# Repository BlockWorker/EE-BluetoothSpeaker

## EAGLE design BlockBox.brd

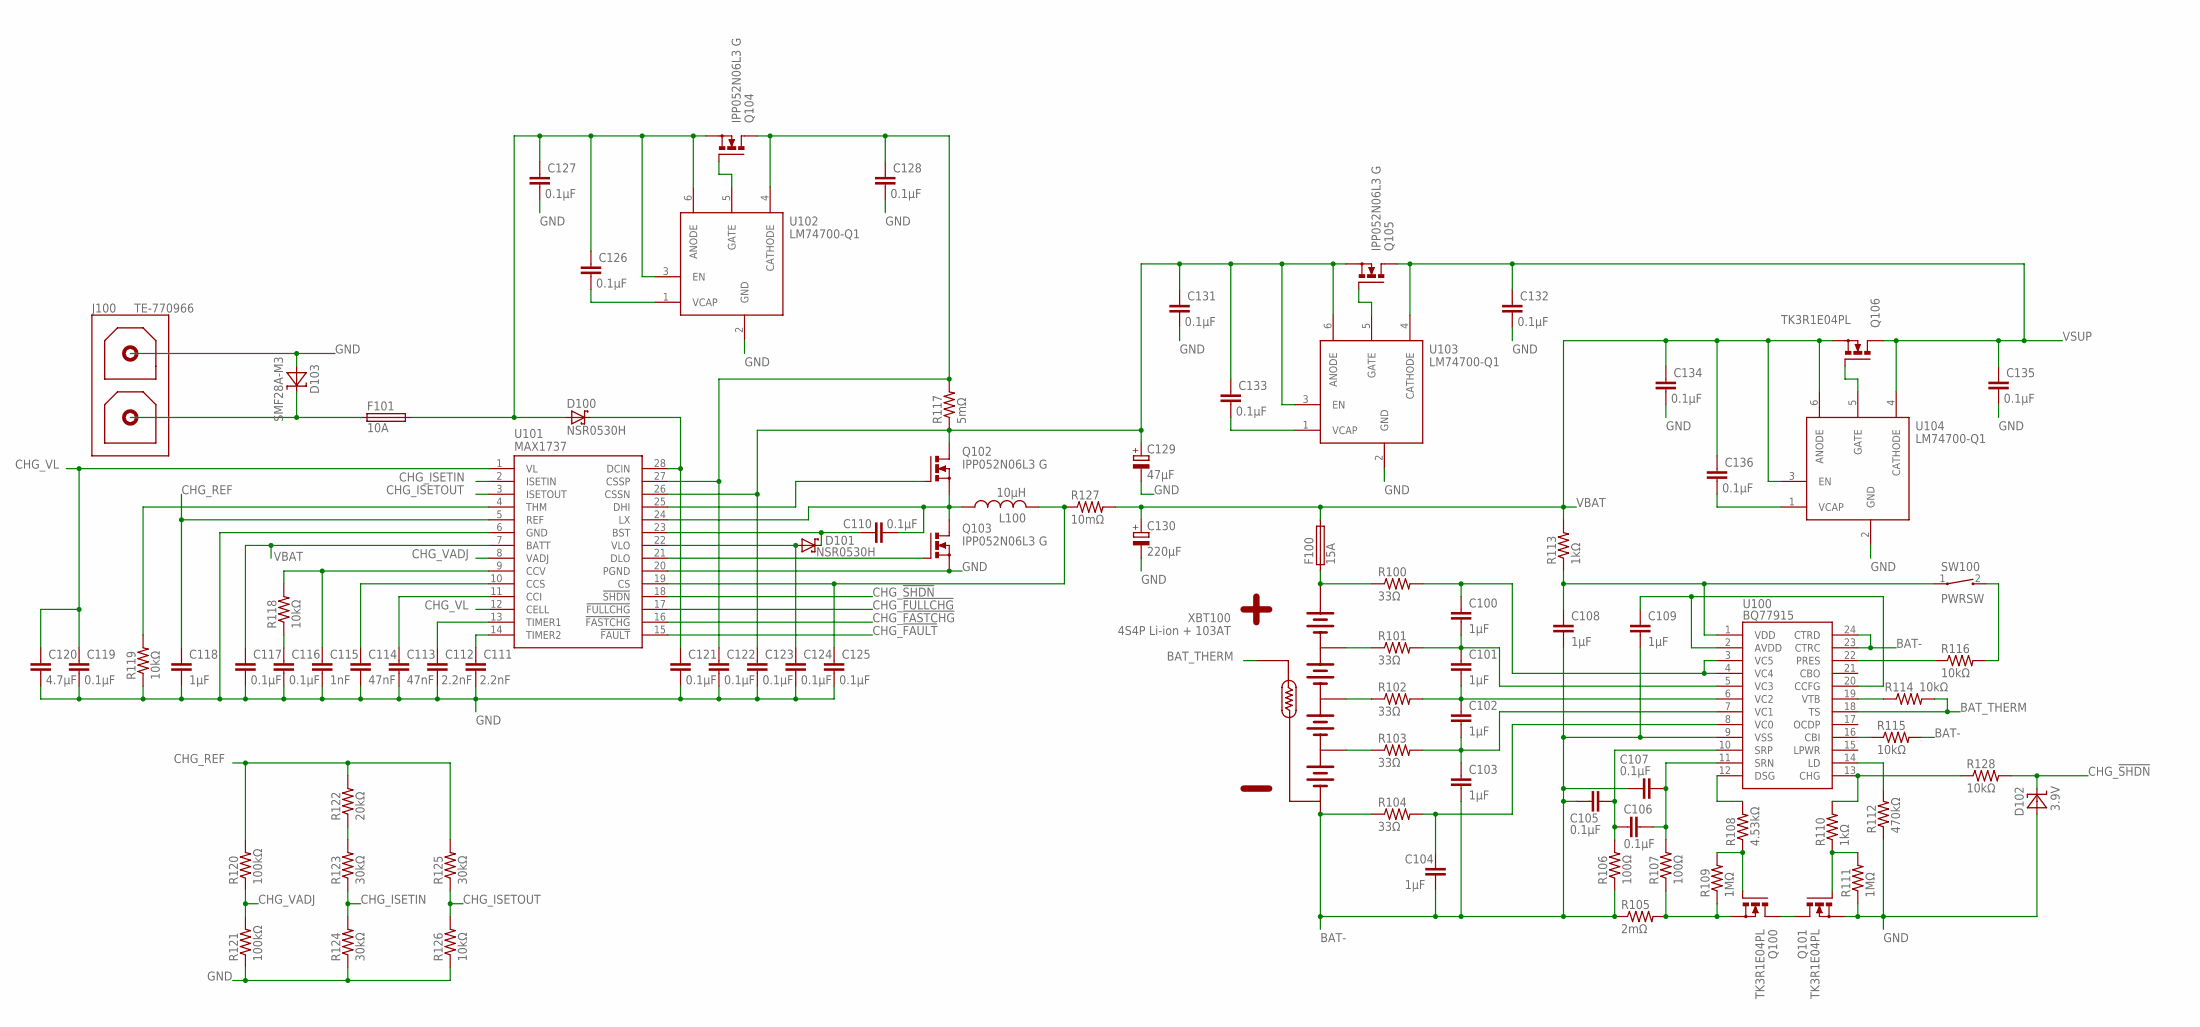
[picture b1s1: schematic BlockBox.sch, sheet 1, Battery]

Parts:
C100, C101, C102, C103, C104, C108, C109, C118: 1µF; C0603
C105, C106, C107, C110, C116, C117, C119, C121, C122, C123, C124, C125, C126, C127, C128, C131, C132, C133, C134, C135, C136: 0.1µF; C0805
C111, C112: 2.2nF; C0603
C113, C114: 47nF; C0603
C115: 1nF; C0603
C120: 4.7µF; C0805
C129: 47µF; E2,5-6
C130: 220µF; E3,5-8
D100, D101: NSR0530H; SOD323
D102: 3.9V; SOD323
D103: SMF28A-M3; DO-219AB
F100: 15A; F2410
F101: 10A; F2410
J100: TE-770966
L100: 10µH; PM5022
Q100, Q101, Q106: TK3R1E04PL; TO220BV
Q102, Q103, Q104, Q105: IPP052N06L3 G; TO220BV
R100, R101, R102, R103, R104: 33Ω; R0603
R105: 2mΩ; R2512
R106, R107: 100Ω; R0603
R108: 4.53kΩ; R0603
R109, R111: 1MΩ; R0603
R110, R113: 1kΩ; R0805
R112: 470kΩ; R0603
R114, R115, R116, R118, R119, R126, R128: 10kΩ; R0805
R117: 5mΩ; R1206
R120, R121: 100kΩ; R0805
R122: 20kΩ; R0603
R123, R124, R125: 30kΩ; R0603
R127: 10mΩ; R1206
SW100: PWRSW; WIRE-2P-SIMPLE
U100: BQ77915; TSSOP24
U101: MAX1737; QSOP28
U102, U103, U104: LM74700-Q1; SOT23-6L
XBT100: 4S4P Li-ion + 103AT; TE-770970

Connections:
BAT-: C103.2, C104.2, C105.1, C107.1, C108.2, C109.2, R104.1, R105.1, R106.1, R115.2, U100.9 (VSS), U100.23 (CTRC), U100.24 (CTRD), XBT100.5 (-), XBT100.6 (-)
BAT-_INT1: Q100.S, R105.2, R107.1, R109.1
BAT-_INT2: Q100.D, Q101.D
BAT_AVDD: C109.1, U100.2 (AVDD), U100.20 (CCFG)
BAT_BAL0: C104.1, R104.2, U100.8 (VC0)
BAT_BAL1: C102.2, C103.1, R103.2, U100.7 (VC1)
BAT_BAL2: C101.2, C102.1, R102.2, U100.6 (VC2)
BAT_BAL3: C100.2, C101.1, R101.2, U100.5 (VC3)
BAT_BAL4: C100.1, R100.2, U100.3 (VC5), U100.4 (VC4)
BAT_CBI: R115.1, U100.16 (CBI)
BAT_CHG_CTL: R110.2, R128.1, U100.13 (CHG)
BAT_CHG_GATE: Q101.G, R110.1, R111.2
BAT_CSN: C106.2, C107.2, R107.2, U100.11 (SRN)
BAT_CSP: C105.2, C106.1, R106.2, U100.10 (SRP)
BAT_DSG_CTL: R108.2, U100.12 (DSG)
BAT_DSG_GATE: Q100.G, R108.1, R109.2
BAT_INT1: R103.1, XBT100.4 (BAL1)
BAT_INT2: R102.1, XBT100.3 (BAL2)
BAT_INT3: R101.1, XBT100.7 (BAL3)
BAT_LD: R112.2, U100.14 (LD)
BAT_PRES: R116.1, U100.22 (PRES)
BAT_PRES_SW: R116.2, SW100.2
BAT_THERM: R114.2, U100.18 (TS), XBT100.8 (THERM1)
BAT_VDD: C108.1, R113.1, SW100.1, U100.1 (VDD)
BAT_VTB: R114.1, U100.19 (VTB)
CHG_!FASTCHG: U101.16 (!FASTCHG); also elsewhere on the board
CHG_!FAULT: U101.15 (!FAULT); also elsewhere on the board
CHG_!FULLCHG: U101.17 (!FULLCHG); also elsewhere on the board
CHG_!SHDN: D102.1 (C), R128.2, U101.18 (!SHDN)
CHG_BST: C110.1, D101.1 (C), U101.23 (BST)
CHG_CCI: C113.1, U101.11 (CCI)
CHG_CCS: C114.1, U101.10 (CCS)
CHG_CCV: C115.1, R118.2, U101.9 (CCV)
CHG_CCV_FILT: C116.1, R118.1
CHG_CS: C125.1, L100.2, R127.1, U101.19 (CS)
CHG_CSSN: C123.1, C129.+, C131.1, C133.1, Q102.D, Q105.S, R117.1, U101.26 (CSSN), U103.3 (EN), U103.6 (ANODE)
CHG_CSSP: C122.1, C128.1, Q104.D, R117.2, U101.27 (CSSP), U102.4 (CATHODE)
CHG_DCIN: C121.1, D100.1 (C), U101.28 (DCIN)
CHG_DHI: Q102.G, U101.25 (DHI)
CHG_DLO: Q103.G, U101.21 (DLO)
CHG_ISETIN: R123.1, R124.2, U101.2 (ISETIN)
CHG_ISETIN_INT: R122.1, R123.2
CHG_ISETOUT: R125.1, R126.2, U101.3 (ISETOUT)
CHG_LX: C110.2, L100.1, Q102.S, Q103.D, U101.24 (LX)
CHG_REF: C118.1, R120.2, R122.2, R125.2, U101.5 (REF)
CHG_THM: R119.2, U101.4 (THM)
CHG_TIMER1: C112.1, U101.13 (TIMER1)
CHG_TIMER2: C111.1, U101.14 (TIMER2)
CHG_VADJ: R120.1, R121.2, U101.8 (VADJ)
CHG_VL: C119.1, C120.1, U101.1 (VL), U101.12 (CELL)
CHG_VLO: C124.1, D101.2 (A), U101.22 (VLO)
GND: C111.2, C112.2, C113.2, C114.2, C115.2, C116.2, C117.2, C118.2, C119.2, C120.2, C121.2, C122.2, C123.2, C124.2, C125.2, C127.2, C128.2, C129.-, C130.-, C131.2, C132.2, C134.2, C135.2, D102.2 (A), D103.A, J100.2, Q101.S, Q103.S, R111.1, R112.1, R119.1, R121.1, R124.1, R126.1, U101.6 (GND), U101.20 (PGND), U102.2 (GND), U103.2 (GND), U104.2 (GND); also elsewhere on the board
VBAT: C117.1, C130.+, C134.1, C136.1, F100.2, Q106.S, R113.2, R127.2, U101.7 (BATT), U104.3 (EN), U104.6 (ANODE); also elsewhere on the board
VBAT_PREFUSE: F100.1, R100.1, XBT100.1 (+), XBT100.2 (+)
VIN_EXT: D103.K (C), F101.1, J100.1
VIN_EXT_FUSED: C126.1, C127.1, D100.2 (A), F101.2, Q104.S, U102.3 (EN), U102.6 (ANODE)
VIN_ID_GATE: Q104.G, U102.5 (GATE)
VIN_ID_VCAP: C126.2, U102.1 (VCAP)
VSUP: C132.1, C135.1, Q105.D, Q106.D, U103.4 (CATHODE), U104.4 (CATHODE); also elsewhere on the board
VSUP_ID1_GATE: Q105.G, U103.5 (GATE)
VSUP_ID1_VCAP: C133.2, U103.1 (VCAP)
VSUP_ID2_GATE: Q106.G, U104.5 (GATE)
VSUP_ID2_VCAP: C136.2, U104.1 (VCAP)

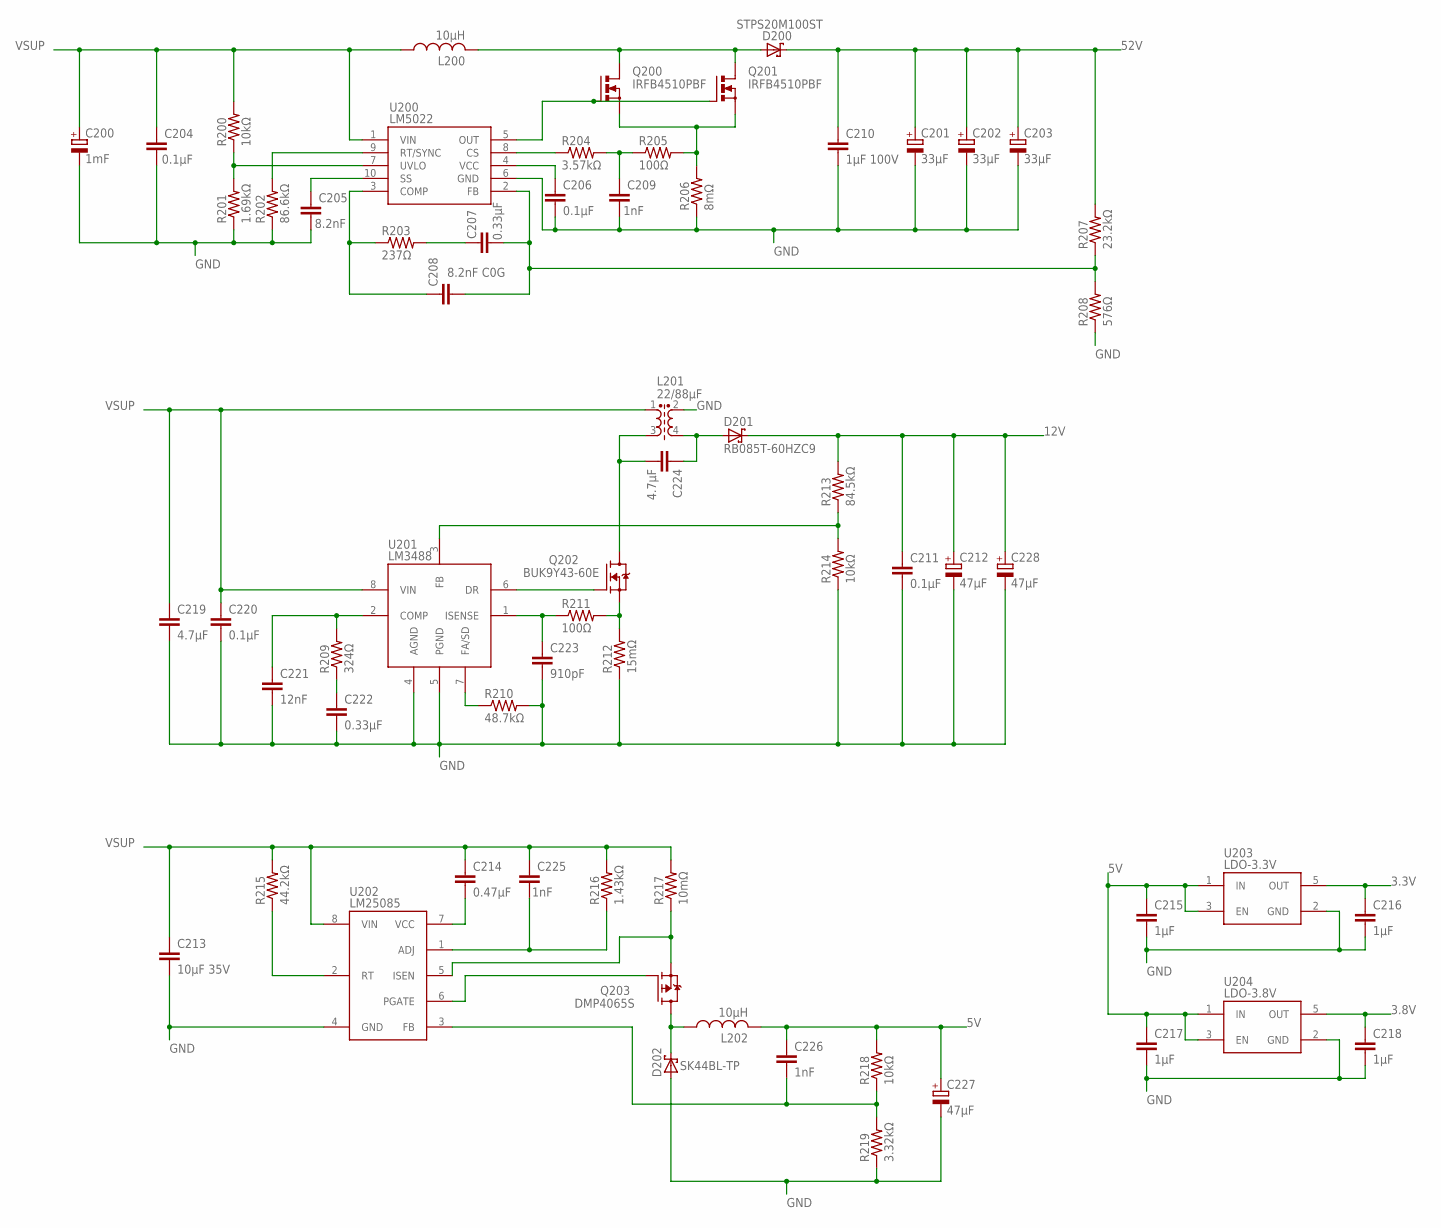
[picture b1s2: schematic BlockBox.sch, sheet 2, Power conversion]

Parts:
C200: 1mF; E7,5-16
C201, C202, C203: 33µF; E3,5-8
C204, C206, C211, C220: 0.1µF; C0805
C205: 8.2nF; C0603
C207, C222: 0.33µF; C050-035X075
C208: 8.2nF C0G; C0603
C209, C225, C226: 1nF; C0603
C210: 1µF 100V; C1206
C212, C227, C228: 47µF; E2,5-6
C213: 10µF 35V; C1206
C214: 0.47µF; C0603
C215, C216, C217, C218: 1µF; C0603
C219, C224: 4.7µF; C0805
C221: 12nF; C0805
C223: 910pF; C0603
D200: STPS20M100ST; TO220ABS
D201: RB085T-60HZC9; TO220ABS
D202: SK44BL-TP; DO-214AA
L200: 10µH; PQ2614B
L201: 22/88µF; SRF1280A
L202: 10µH; SRN1060
Q200, Q201: IRFB4510PBF; TO220BV
Q202: BUK9Y43-60E; SOT669
Q203: DMP4065S; SOT23
R200, R214, R218: 10kΩ; R0805
R201: 1.69kΩ; R0603
R202: 86.6kΩ; R0603
R203: 237Ω; R0603
R204: 3.57kΩ; R0603
R205, R211: 100Ω; R0603
R206: 8mΩ; R1206
R207: 23.2kΩ; R0603
R208: 576Ω; R0603
R209: 324Ω; R0603
R210: 48.7kΩ; R0603
R212: 15mΩ; R0612
R213: 84.5kΩ; R0603
R215: 44.2kΩ; R0603
R216: 1.43kΩ; R0603
R217: 10mΩ; R1206
R219: 3.32kΩ; R0603
U200: LM5022; VSSOP10
U201: LM3488; VSSOP8
U202: LM25085; VSSOP8
U203: LDO-3.3V; SOT23-5L
U204: LDO-3.8V; SOT23-5L

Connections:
3.3V: C216.1, U203.5 (OUT); also elsewhere on the board
3.8V: C218.1, U204.5 (OUT); also elsewhere on the board
5V: C215.1, C217.1, C226.1, C227.+, L202.2, R218.2, U203.1 (IN), U203.3 (EN), U204.1 (IN), U204.3 (EN); also elsewhere on the board
12V: C211.1, C212.+, C228.+, D201.C, R213.2; also elsewhere on the board
52V: C201.+, C202.+, C203.+, C210.1, D200.C, R207.2; also elsewhere on the board
BOOST_COMP: C208.1, R203.1, U200.3 (COMP)
BOOST_COMP_INT: C207.1, R203.2
BOOST_CS: R204.1, U200.8 (CS)
BOOST_CS_FILTER: C209.1, R204.2, R205.1
BOOST_FB: C207.2, C208.2, R207.1, R208.2, U200.2 (FB)
BOOST_RT: R202.2, U200.9 (RT/SYNC)
BOOST_SS: C205.1, U200.10 (SS)
BOOST_SW_DRAIN: D200.A1 (A), D200.A2 (A), L200.2, Q200.D, Q201.D
BOOST_SW_GATE: Q200.G, Q201.G, U200.5 (OUT)
BOOST_SW_SOURCE: Q200.S, Q201.S, R205.2, R206.2
BOOST_UVLO: R200.1, R201.2, U200.7 (UVLO)
BOOST_VCC: C206.1, U200.4 (VCC)
BUCK_ADJ: C225.2, R216.1, U202.1 (ADJ)
BUCK_FB: C226.2, R218.1, R219.2, U202.3 (FB)
BUCK_RT: R215.1, U202.2 (RT)
BUCK_SW_DRAIN: Q203.2 (S), R217.1, U202.5 (ISEN)
BUCK_SW_GATE: Q203.1 (G), U202.6 (PGATE)
BUCK_SW_SOURCE: D202.K (C), L202.1, Q203.3 (D)
BUCK_VCC: C214.2, U202.7 (VCC)
GND: C200.-, C201.-, C202.-, C203.-, C204.2, C205.2, C206.2, C209.2, C210.2, C211.2, C212.-, C213.2, C215.2, C216.2, C217.2, C218.2, C219.2, C220.2, C221.2, C222.2, C223.2, C227.-, C228.-, D202.A, L201.2 (S1), R201.1, R202.1, R206.1, R208.1, R210.2, R212.1, R214.1, R219.1, U200.6 (GND), U201.4 (AGND), U201.5 (PGND), U202.4 (GND), U203.2 (GND), U204.2 (GND); also elsewhere on the board
SEPIC_COMP: C221.1, R209.2, U201.2 (COMP)
SEPIC_COMP_INT: C222.1, R209.1
SEPIC_FA: R210.1, U201.7 (FA/SD)
SEPIC_FB: R213.1, R214.2, U201.3 (FB)
SEPIC_ISENSE: C223.1, R211.1, U201.1 (ISENSE)
SEPIC_PREDIODE: C224.1, D201.A1 (A), D201.A2 (A), L201.4 (S2)
SEPIC_SW_DRAIN: C224.2, L201.3 (P2), Q202.MB (D)
SEPIC_SW_GATE: Q202.4 (G), U201.6 (DR)
SEPIC_SW_SOURCE: Q202.1 (S), Q202.2 (S), Q202.3 (S), R211.2, R212.2
VSUP: C200.+, C204.1, C213.1, C214.1, C219.1, C220.1, C225.1, L200.1, L201.1, R200.2, R215.2, R216.2, R217.2, U200.1 (VIN), U201.8 (VIN), U202.8 (VIN); also elsewhere on the board

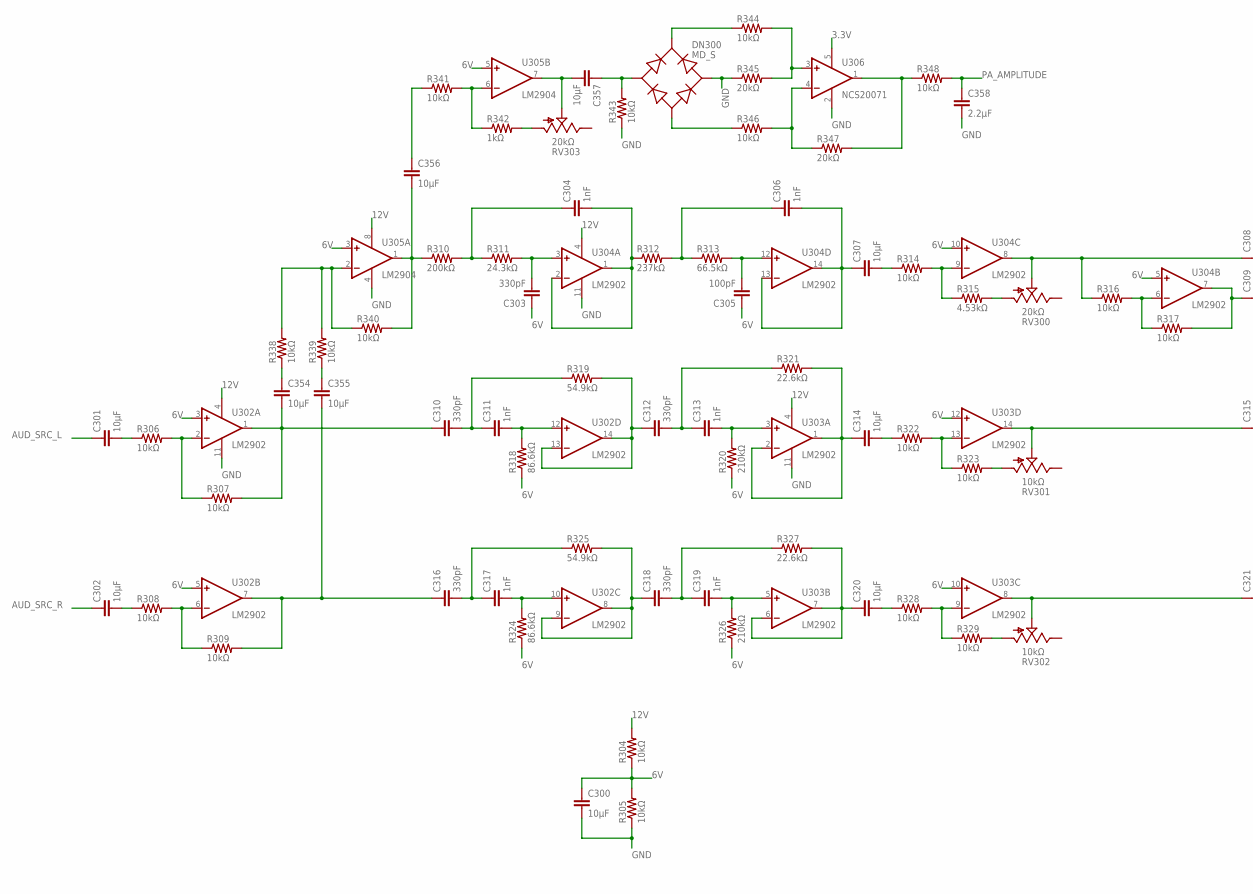
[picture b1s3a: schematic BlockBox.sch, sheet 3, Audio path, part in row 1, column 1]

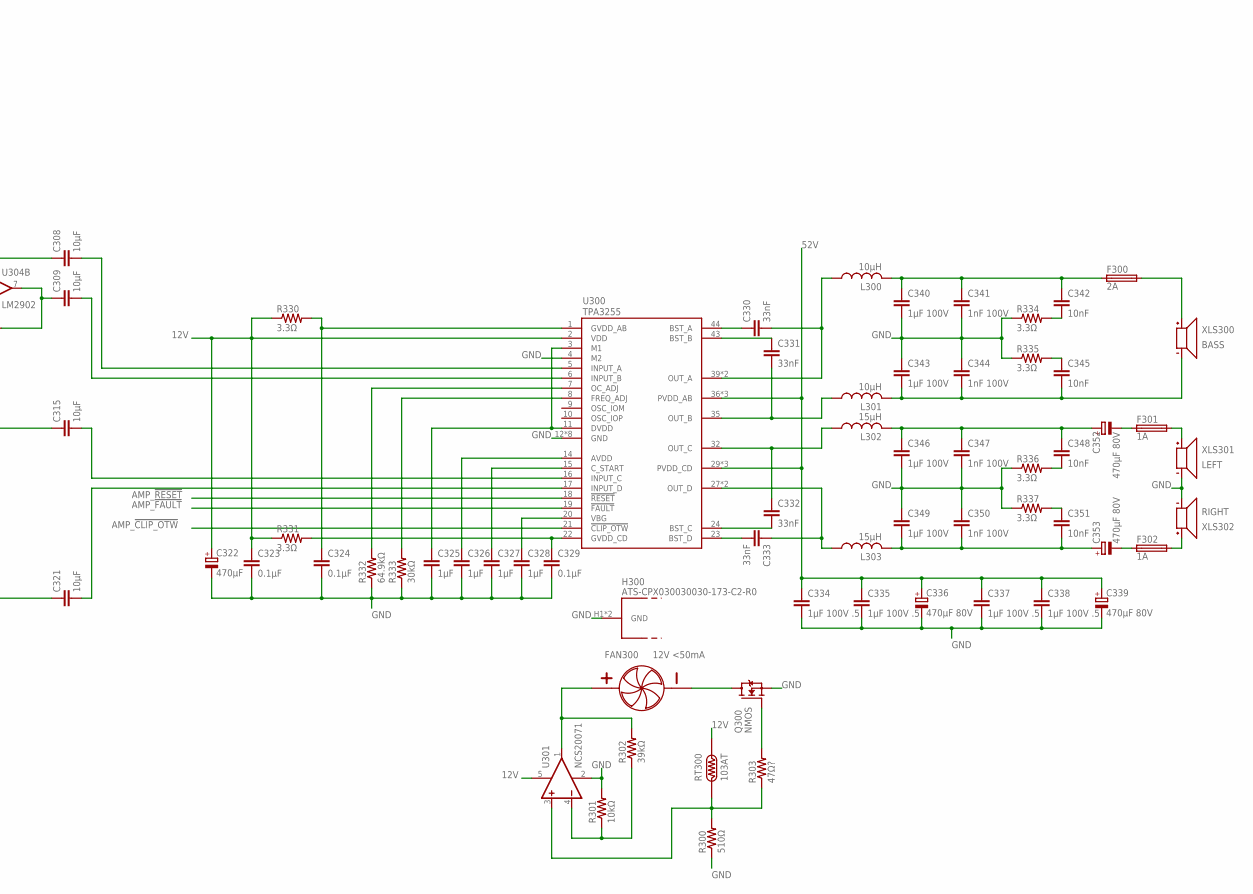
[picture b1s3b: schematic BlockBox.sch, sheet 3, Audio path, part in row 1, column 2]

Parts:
C300, C301, C302, C307, C314, C320, C354, C355, C356, C357: 10µF; C0805
C303, C310, C312, C316, C318: 330pF; C0603
C304, C306, C311, C313, C317, C319: 1nF; C0603
C305: 100pF; C0603
C308, C309, C315, C321: 10µF; C0603
C322: 470µF; E3,5-8
C323, C324, C329: 0.1µF; C0805
C325, C326, C327, C328: 1µF; C0603
C330, C331, C332, C333: 33nF; C0805
C334, C335, C337, C338: 1µF 100V .5; C1206
C336, C339, C352, C353: 470µF 80V; E5-13
C340, C343, C346, C349: 1µF 100V; C1206
C341, C344, C347, C350: 1nF 100V; C0603
C342, C345, C348, C351: 10nF; C0603
C358: 2.2µF; C0603
DN300: MD_S; MD-S-4
F300: 2A; MRF_FUSE
F301, F302: 1A; MRF_FUSE
FAN300: 12V <50mA; WIRE-2P-SIMPLE
H300: ATS-CPX030030030-173-C2-R0
L300, L301: 10µH; RCH8011
L302, L303: 15µH; RCH8011
Q300: NMOS; SOT23
R300: 510Ω; R0603
R301, R304, R305, R306, R307, R308, R309, R314, R316, R317, R322, R323, R328, R329, R338, R339, R340, R341, R343, R344, R346, R348: 10kΩ; R0805
R302: 39kΩ; R0603
R303: 47Ω?; R0603
R310: 200kΩ; R0603
R311: 24.3kΩ; R0603
R312: 237kΩ; R0603
R313: 66.5kΩ; R0603
R315: 4.53kΩ; R0603
R318, R324: 86.6kΩ; R0603
R319, R325: 54.9kΩ; R0603
R320, R326: 210kΩ; R0603
R321, R327: 22.6kΩ; R0603
R330, R331, R334, R335, R336, R337: 3.3Ω; R0805
R332: 64.9kΩ; R0603
R333: 30kΩ; R0603
R342: 1kΩ; R0805
R345, R347: 20kΩ; R0603
RT300: 103AT; WIRE-2P-SIMPLE
RV300, RV303: 20kΩ; TC33X-2
RV301, RV302: 10kΩ; TC33X-2
U300: TPA3255; TSSOP44
U301, U306: NCS20071; TSOP-5
U302, U303, U304: LM2902; TSSOP14
U305: LM2904; MSOP8
XLS300: BASS; TE-770966
XLS301: LEFT; TE-770966
XLS302: RIGHT; TE-770966

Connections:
3.3V: U306.5 (V+); also elsewhere on the board
6V: C300.1, C303.1, C305.1, R304.1, R305.2, R318.1, R320.1, R324.1, R326.1, U302.3 (+IN), U302.5 (+IN), U303.10 (+IN), U303.12 (+IN), U304.5 (+IN), U304.10 (+IN), U305.3 (+IN), U305.5 (+IN)
12V: C322.+, C323.1, R304.2, R330.1, R331.1, RT300.1, U300.2 (VDD), U301.5 (V+), U302.4 (V+), U303.4 (V+), U304.4 (V+), U305.8 (V+); also elsewhere on the board
52V: C334.1, C335.1, C336.+, C337.1, C338.1, C339.+, U300.29 (PVDD_CD), U300.30 (PVDD_CD), U300.31 (PVDD_CD), U300.36 (PVDD_AB), U300.37 (PVDD_AB), U300.38 (PVDD_AB); also elsewhere on the board
AMP_!CLIP_OTW: U300.21 (!CLIP_OTW); also elsewhere on the board
AMP_!FAULT: U300.19 (!FAULT); also elsewhere on the board
AMP_!RESET: U300.18 (!RESET); also elsewhere on the board
AMP_AVDD: C326.1, U300.14 (AVDD)
AMP_A_FILT: C340.1, C341.1, C342.1, F300.1, L300.2
AMP_A_FILT_INT: C342.2, R334.2
AMP_A_FUSED: F300.2, XLS300.2 (+)
AMP_BST_A: C330.1, U300.44 (BST_A)
AMP_BST_B: C331.1, U300.43 (BST_B)
AMP_BST_C: C332.2, U300.24 (BST_C)
AMP_BST_D: C333.2, U300.23 (BST_D)
AMP_B_FILT: C343.2, C344.2, C345.2, L301.2, XLS300.1 (-)
AMP_B_FILT_INT: C345.1, R335.2
AMP_CSTART: C327.1, U300.15 (C_START)
AMP_C_COUPLED: C352.-, F301.1
AMP_C_FILT: C346.1, C347.1, C348.1, C352.+, L302.2
AMP_C_FILT_INT: C348.2, R336.2
AMP_C_FUSED: F301.2, XLS301.2 (+)
AMP_DVDD: C325.1, U300.3 (M1), U300.11 (DVDD)
AMP_D_COUPLED: C353.-, F302.1
AMP_D_FILT: C349.2, C350.2, C351.2, C353.+, L303.2
AMP_D_FILT_INT: C351.1, R337.2
AMP_D_FUSED: F302.2, XLS302.2 (+)
AMP_FAN_+: FAN300.1 (+), R302.2, U301.1 (OUT)
AMP_FAN_-: FAN300.2 (-), Q300.3 (D)
AMP_FAN_FB: R301.1, R302.1, U301.4 (-IN)
AMP_FAN_GATE: Q300.1 (G), R303.2
AMP_FAN_SENSE: R300.2, R303.1, RT300.2, U301.3 (+IN)
AMP_FREQ_ADJ: R333.2, U300.8 (FREQ_ADJ)
AMP_GVDD_AB: C324.1, R330.2, U300.1 (GVDD_AB)
AMP_GVDD_CD: C329.1, R331.2, U300.22 (GVDD_CD)
AMP_IN_A: C308.2, U300.5 (INPUT_A)
AMP_IN_B: C309.2, U300.6 (INPUT_B)
AMP_IN_C: C315.2, U300.16 (INPUT_C)
AMP_IN_D: C321.2, U300.17 (INPUT_D)
AMP_OC_ADJ: R332.2, U300.7 (OC_ADJ)
AMP_OUT_A: C330.2, L300.1, U300.39 (OUT_A), U300.40 (OUT_A)
AMP_OUT_B: C331.2, L301.1, U300.35 (OUT_B)
AMP_OUT_C: C332.1, L302.1, U300.32 (OUT_C)
AMP_OUT_D: C333.1, L303.1, U300.27 (OUT_D), U300.28 (OUT_D)
AMP_VBG: C328.1, U300.20 (VBG)
AUD_SRC_L: C301.1; also elsewhere on the board
AUD_SRC_R: C302.1; also elsewhere on the board
GND: C300.2, C322.-, C323.2, C324.2, C325.2, C326.2, C327.2, C328.2, C329.2, C334.2, C335.2, C336.-, C337.2, C338.2, C339.-, C340.2, C341.2, C343.1, C344.1, C346.2, C347.2, C349.1, C350.1, C358.2, DN300.~2 (AC2), H300.H1, H300.H2, Q300.2 (S), R300.1, R301.2, R305.1, R332.1, R333.1, R334.1, R335.1, R336.1, R337.1, R343.1, R345.1, U300.4 (M2), U300.12 (GND), U300.13 (GND), U300.25 (GND), U300.26 (GND), U300.33 (GND), U300.34 (GND), U300.41 (GND), U300.42 (GND), U301.2 (V-), U302.11 (V-), U303.11 (V-), U304.11 (V-), U305.4 (V-), U306.2 (V-), XLS301.1 (-), XLS302.1 (-); also elsewhere on the board
PA_AF_DIFF+: R344.2, R345.2, U306.3 (+IN)
PA_AF_DIFF-: R346.2, R347.1, U306.4 (-IN)
PA_AF_FB: R341.2, R342.1, U305.6 (-IN)
PA_AF_FB_VAR: R342.2, RV303.1 (A)
PA_AF_IN: C356.1, R341.1
PA_AF_INT: C357.2, RV303.2 (S), U305.7 (OUT)
PA_AF_INT_COUPLED: C357.1, DN300.~1 (AC1), R343.2
PA_AF_OUT: R347.2, R348.1, U306.1 (OUT)
PA_AF_RECT+: DN300.+ (DC+), R344.1
PA_AF_RECT-: DN300.- (DC-), R346.1
PA_AMPLITUDE: C358.1, R348.2; also elsewhere on the board
PA_B1_FB: C304.1, R310.2, R311.1
PA_B1_FILT: C303.2, R311.2, U304.3 (+IN)
PA_B1_OUT: C304.2, R312.1, U304.1 (OUT), U304.2 (-IN)
PA_B2_FB: C306.1, R312.2, R313.1
PA_B2_FILT: C305.2, R313.2, U304.12 (+IN)
PA_B2_OUT: C306.2, C307.1, U304.13 (-IN), U304.14 (OUT)
PA_BL_COUPLE: C354.1, R338.1
PA_BR_COUPLE: C355.1, R339.1
PA_B_COUPLE: C307.2, R314.1
PA_B_FINAL+: C308.1, R316.1, RV300.2 (S), U304.8 (OUT)
PA_B_FINAL-: C309.1, R317.2, U304.7 (OUT)
PA_B_GFB: R314.2, R315.1, U304.9 (-IN)
PA_B_GFB_VAR: R315.2, RV300.1 (A)
PA_B_IFB: R316.2, R317.1, U304.6 (-IN)
PA_B_IN_BUFFERED: C356.2, R310.1, R340.2, U305.1 (OUT)
PA_B_IN_SUM: R338.2, R339.2, R340.1, U305.2 (-IN)
PA_L1_FB: C310.2, C311.1, R319.1
PA_L1_FILT: C311.2, R318.2, U302.12 (+IN)
PA_L1_OUT: C312.1, R319.2, U302.13 (-IN), U302.14 (OUT)
PA_L2_FB: C312.2, C313.1, R321.1
PA_L2_FILT: C313.2, R320.2, U303.3 (+IN)
PA_L2_OUT: C314.1, R321.2, U303.1 (OUT), U303.2 (-IN)
PA_L_COUPLE: C314.2, R322.1
PA_L_FINAL: C315.1, RV301.2 (S), U303.14 (OUT)
PA_L_GFB: R322.2, R323.1, U303.13 (-IN)
PA_L_GFB_VAR: R323.2, RV301.1 (A)
PA_L_IN_BUFFERED: C310.1, C354.2, R307.2, U302.1 (OUT)
PA_L_IN_COUPLE: C301.2, R306.1
PA_L_IN_FB: R306.2, R307.1, U302.2 (-IN)
PA_R1_FB: C316.2, C317.1, R325.1
PA_R1_FILT: C317.2, R324.2, U302.10 (+IN)
PA_R1_OUT: C318.1, R325.2, U302.8 (OUT), U302.9 (-IN)
PA_R2_FB: C318.2, C319.1, R327.1
PA_R2_FILT: C319.2, R326.2, U303.5 (+IN)
PA_R2_OUT: C320.1, R327.2, U303.6 (-IN), U303.7 (OUT)
PA_R_COUPLE: C320.2, R328.1
PA_R_FINAL: C321.1, RV302.2 (S), U303.8 (OUT)
PA_R_GFB: R328.2, R329.1, U303.9 (-IN)
PA_R_GFB_VAR: R329.2, RV302.1 (A)
PA_R_IN_BUFFERED: C316.1, C355.2, R309.2, U302.7 (OUT)
PA_R_IN_COUPLE: C302.2, R308.1
PA_R_IN_FB: R308.2, R309.1, U302.6 (-IN)

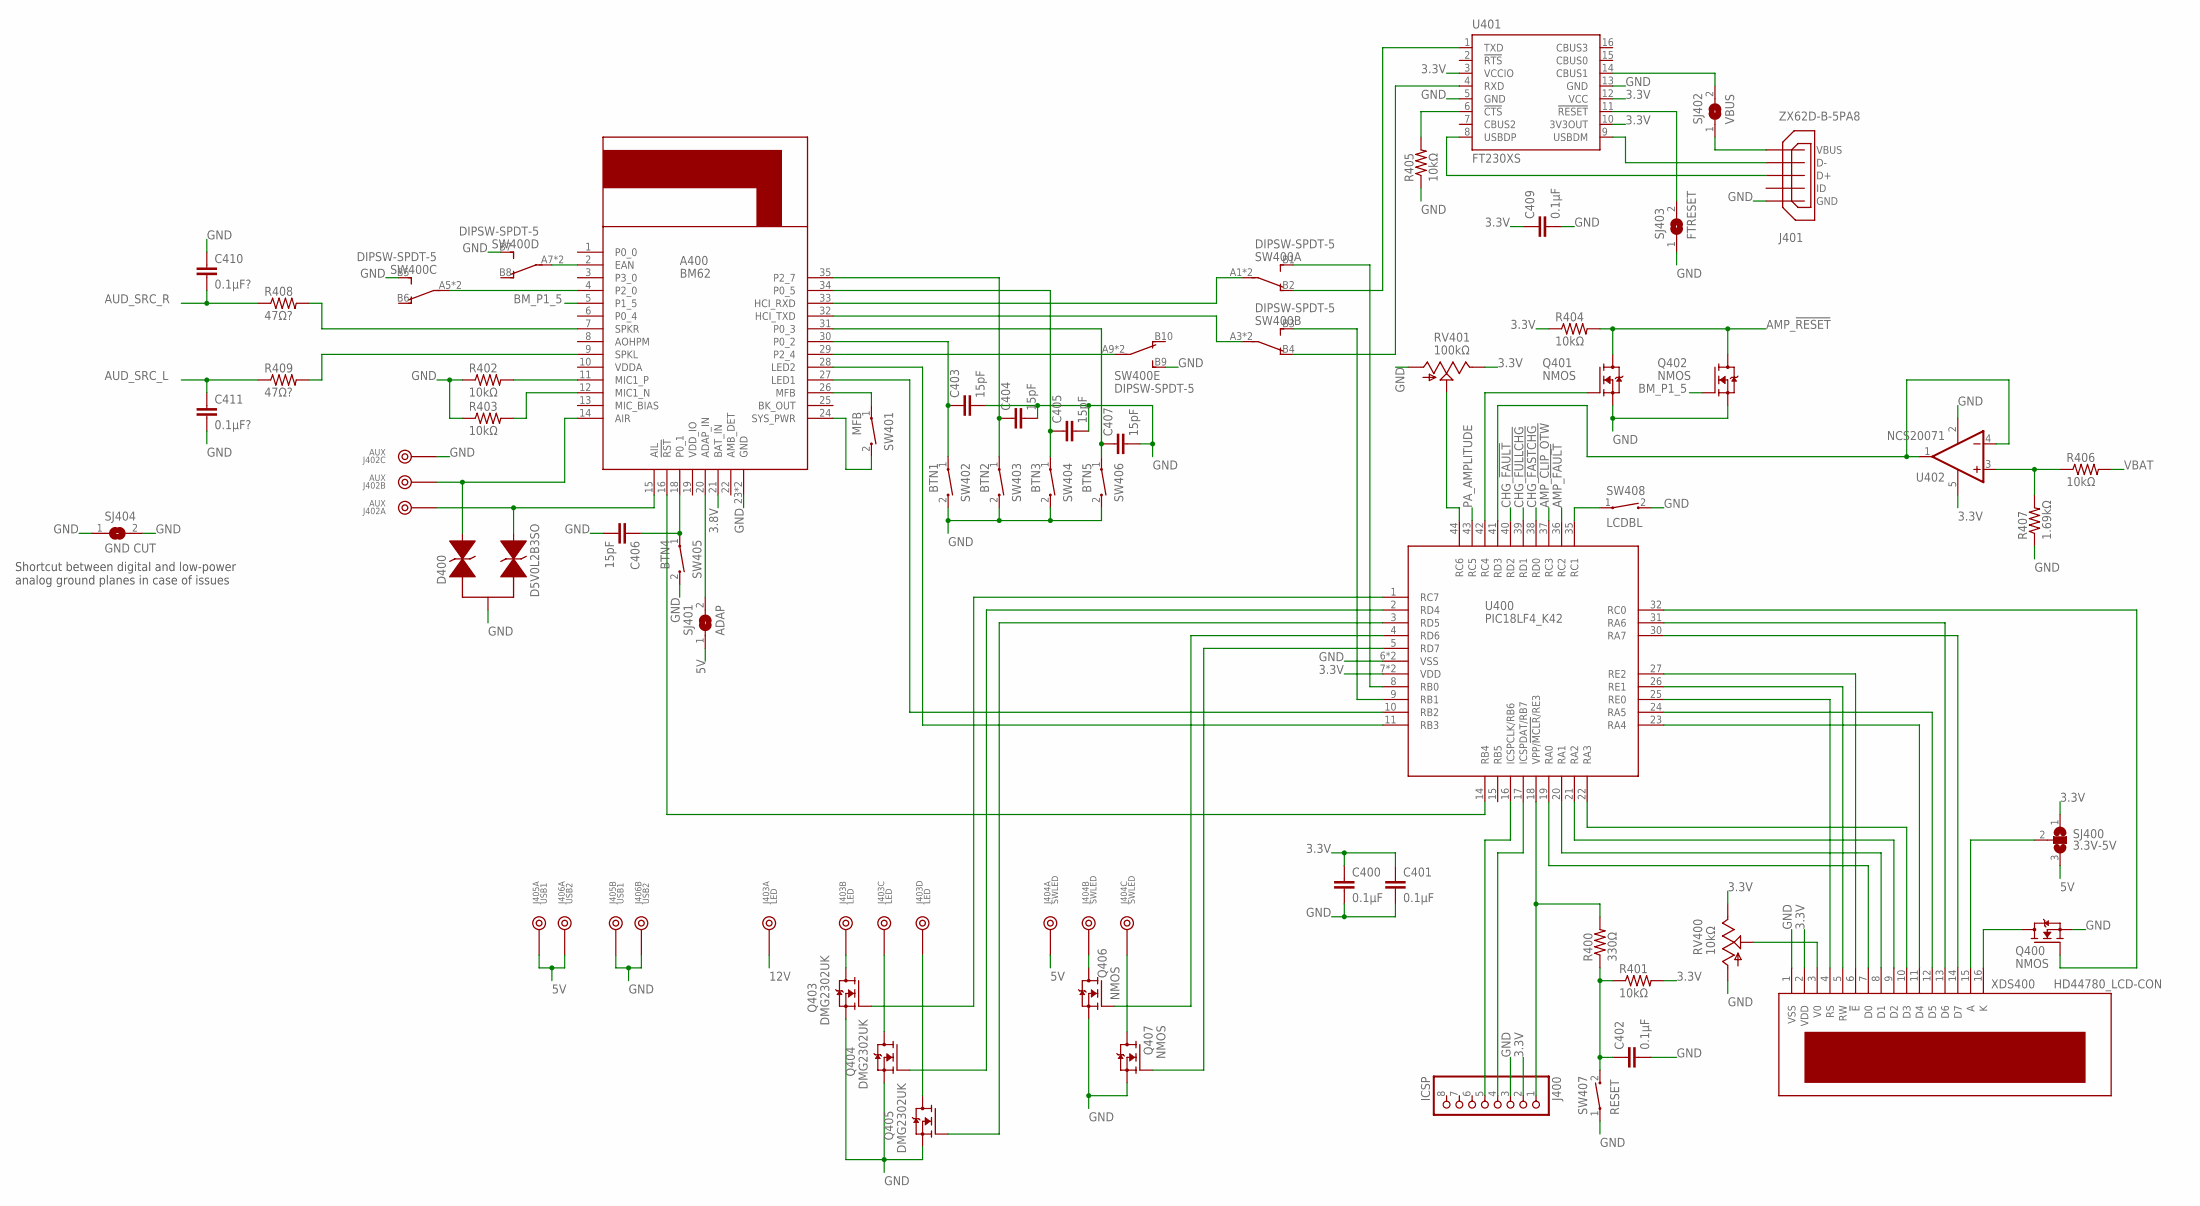
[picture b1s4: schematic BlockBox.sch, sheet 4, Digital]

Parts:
A400: BM62
C400, C401, C402, C409: 0.1µF; C0805
C403, C404, C405, C406, C407: 15pF; C0603
C410, C411: 0.1µF?; C0805
D400: D5V0L2B3SO; SOT23
J400: ICSP; 1X08
J401: ZX62D-B-5PA8
J402: AUX; 3PIN
J403: LED; 4PIN
J404: SWLED; 3PIN
J405: USB1; 2PIN
J406: USB2; 2PIN
Q400, Q401, Q402, Q406, Q407: NMOS; SOT23
Q403, Q404, Q405: DMG2302UK; SOT23
R400: 330Ω; R0805
R401, R402, R403, R404, R405, R406: 10kΩ; R0805
R407: 1.69kΩ; R0603
R408, R409: 47Ω?; R0603
RV400: 10kΩ; TC33X-2
RV401: 100kΩ; WIRE-3P-SIMPLE
SJ400: 3.3V-5V; SJ_2
SJ401: ADAP; SJ
SJ402: VBUS; SJ
SJ403: FTRESET; SJ
SJ404: GND CUT; SJ
SW400: DIPSW-SPDT-5; DIPSW-10
SW401: MFB; WIRE-2P-SIMPLE
SW402: BTN1; WIRE-2P-SIMPLE
SW403: BTN2; WIRE-2P-SIMPLE
SW404: BTN3; WIRE-2P-SIMPLE
SW405: BTN4; WIRE-2P-SIMPLE
SW406: BTN5; WIRE-2P-SIMPLE
SW407: RESET; WIRE-2P-SIMPLE
SW408: LCDBL; WIRE-2P-SIMPLE
U400: PIC18LF4_K42; TQFP44
U401: FT230XS; SSOP16
U402: NCS20071; TSOP-5
XDS400: HD44780_LCD-CON; 2X8PIN

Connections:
3.3V: C400.1, C401.1, C409.1, J400.2, R401.2, R404.1, RV400.3 (E), RV401.3 (E), SJ400.1, U400.7 (VDD), U400.28 (VDD), U401.3 (VCCIO), U401.10 (3V3OUT), U401.12 (VCC), U402.5 (V+), XDS400.2 (VDD); also elsewhere on the board
3.8V: A400.21 (BAT_IN); also elsewhere on the board
5V: J404.1, J405.1, J406.1, SJ400.3, SJ401.1; also elsewhere on the board
12V: J403.1; also elsewhere on the board
AMP_!CLIP_OTW: U400.37 (RC3); also elsewhere on the board
AMP_!FAULT: U400.36 (RC2); also elsewhere on the board
AMP_!RESET: Q401.3 (D), Q402.3 (D), R404.2; also elsewhere on the board
AUD_SRC_L: C411.1, R409.1; also elsewhere on the board
AUD_SRC_R: C410.2, R408.1; also elsewhere on the board
BM_!RST: A400.16 (!RST), U400.14 (RB4)
BM_ADAP_IN: A400.20 (ADAP_IN), SJ401.2
BM_AIL: A400.15 (AIL), D400.2, J402.1
BM_AIR: A400.14 (AIR), D400.1, J402.2
BM_EAN: A400.2 (EAN), SW400.A7, SW400.A8
BM_HCI_RXD: A400.33 (HCI_RXD), SW400.A1, SW400.A2
BM_HCI_TXD: A400.32 (HCI_TXD), SW400.A3, SW400.A4
BM_LED1: A400.27 (LED1), U400.10 (RB2)
BM_LED2: A400.28 (LED2), U400.11 (RB3)
BM_MFB: A400.26 (MFB), SW401.1
BM_MIC_N: A400.12 (MIC1_N), R403.2
BM_MIC_P: A400.11 (MIC1_P), R402.2
BM_P0_1: A400.18 (P0_1), C406.1, SW405.1
BM_P0_2: A400.30 (P0_2), C403.1, SW402.1
BM_P0_3: A400.31 (P0_3), C407.1, SW406.1
BM_P0_5: A400.34 (P0_5), C405.1, SW404.1
BM_P1_5: A400.5 (P1_5), Q402.1 (G)
BM_P2_0: A400.4 (P2_0), SW400.A5, SW400.A6
BM_P2_4: A400.29 (P2_4), SW400.A9, SW400.A10
BM_P2_7: A400.35 (P2_7), C404.1, SW403.1
BM_SPKL: A400.9 (SPKL), R409.2
BM_SPKR: A400.7 (SPKR), R408.2
BM_SYS_PWR: A400.24 (SYS_PWR), SW401.2
CHG_!FASTCHG: U400.38 (RD0); also elsewhere on the board
CHG_!FAULT: U400.40 (RD2); also elsewhere on the board
CHG_!FULLCHG: U400.39 (RD1); also elsewhere on the board
FT_!CTS: R405.2, U401.6 (!CTS)
FT_!RESET: SJ403.2, U401.11 (!RESET)
FT_RXD: SW400.B4 (O), U401.4 (RXD)
FT_TXD: SW400.B2 (O), U401.1 (TXD)
FT_VBUS_SENSE: SJ402.2, U401.14 (CBUS1)
GND: A400.23 (GND), A400.37 (GND), C400.2, C401.2, C402.2, C403.2, C404.2, C405.2, C406.2, C407.2, C409.2, C410.1, C411.2, D400.3 (C), J400.3, J401.5 (GND), J401.S1 (GND), J401.S2 (GND), J401.S3 (GND), J401.S4 (GND), J402.3, J405.2, J406.2, Q400.2 (S), Q401.2 (S), Q402.2 (S), Q403.2 (S), Q404.2 (S), Q405.2 (S), Q406.2 (S), Q407.2 (S), R402.1, R403.1, R405.1, R407.1, RV400.1 (A), RV401.1 (A), SJ403.1, SJ404.1, SJ404.2, SW400.B5 (S), SW400.B7 (S), SW400.B9 (S), SW402.2, SW403.2, SW404.2, SW405.2, SW406.2, SW407.1, SW408.2, U400.6 (VSS), U400.29 (VSS), U401.5 (GND), U401.13 (GND), U402.2 (V-), XDS400.1 (VSS); also elsewhere on the board
LCD_!E: U400.27 (RE2), XDS400.6 (!E)
LCD_A: SJ400.2, XDS400.15 (A)
LCD_BL_EN: Q400.1 (G), U400.32 (RC0)
LCD_D0: U400.19 (RA0), XDS400.7 (D0)
LCD_D1: U400.20 (RA1), XDS400.8 (D1)
LCD_D2: U400.21 (RA2), XDS400.9 (D2)
LCD_D3: U400.22 (RA3), XDS400.10 (D3)
LCD_D4: U400.23 (RA4), XDS400.11 (D4)
LCD_D6: U400.31 (RA6), XDS400.13 (D6)
LCD_D7: U400.30 (RA7), XDS400.14 (D7)
LCD_K: Q400.3 (D), XDS400.16 (K)
LCD_RS: U400.25 (RE0), XDS400.4 (RS)
LCD_RW: U400.26 (RE1), XDS400.5 (RW)
LCD_V0: RV400.2 (S), XDS400.3 (V0)
LDC_D5: U400.24 (RA5), XDS400.12 (D5)
LED_B: J403.4, Q405.3 (D)
LED_G: J403.2, Q403.3 (D)
LED_R: J403.3, Q404.3 (D)
MCU_!MCLR: J400.1, R400.2, U400.18 (VPP/!MCLR!/RE3)
MCU_!MCLR!_FILTERED: C402.1, R400.1, R401.1, SW407.2
MCU_AMP_RESET: Q401.1 (G), U400.42 (RC4)
MCU_BAT_SENSE: U400.41 (RD3), U402.1 (OUT), U402.4 (-IN)
MCU_BAT_VDIV: R406.1, R407.2, U402.3 (+IN)
MCU_BL_SW: SW408.1, U400.35 (RC1)
MCU_ICSPCLK: J400.5, U400.16 (ICSPCLK/RB6)
MCU_ICSPDAT: J400.4, U400.17 (ICSPDAT/RB7)
MCU_LED_B: Q405.1 (G), U400.3 (RD5)
MCU_LED_G: Q403.1 (G), U400.1 (RC7)
MCU_LED_POT: RV401.2 (S), U400.44 (RC6)
MCU_LED_R: Q404.1 (G), U400.2 (RD4)
MCU_SWLED_MAIN: Q406.1 (G), U400.4 (RD6)
MCU_SWLED_PWR: Q407.1 (G), U400.5 (RD7)
MCU_UART_RX: SW400.B3 (S), U400.9 (RB1)
MCU_UART_TX: SW400.B1 (S), U400.8 (RB0)
PA_AMPLITUDE: U400.43 (RC5); also elsewhere on the board
SWLED_MAIN: J404.2, Q406.3 (D)
SWLED_PWR: J404.3, Q407.3 (D)
USB_D+: J401.3 (D+), U401.8 (USBDP)
USB_D-: J401.2 (D-), U401.9 (USBDM)
USB_VBUS: J401.1 (VBUS), SJ402.1
VBAT: R406.2; also elsewhere on the board

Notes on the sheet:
Shortcut between digital and low-power analog ground planes in case of issues

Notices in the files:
BlockBox.brd:
©2019 BlockWorker
